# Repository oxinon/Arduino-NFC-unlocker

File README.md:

# Arduino-NFC-unlocker

<p><center></center></p>

Arduino NFC unlocker with NFC-bridge from Elecfreaks and a small circut for RGB LED and Optokopler, that works like a normal HID, no driver is needed. This will enter a previously stored password, an up arrow key can also be entered beforehand to unlock the screen.
<br>
YouTube Video of the NFC unlocker: https://www.youtube.com/watch?v=7boodr89aAs
<br>
<br>

* * *

<b>Index of this project</b>

+ [Read UID from NFC Tag](#readuid)
+ [Setting your password](#setpasswd)
+ [Eagle circut files](#eagle)
+ [Part list](#parts)

* * *
<br>
<h2>Read UID from NFC Tag</h2>

<p></a></p>

<h2>Setting your password</h2>

<h2>Eagle circut files</h2>

<p></a></p>

<h2>Part list</h2>
NFC brigde by elecfreaks
LED1: SMD RGB LED 1x<br>
LED2: SMD yelow LED 1208 1x<br>
R1,R2: SMD  10Ω Resistor 1208  2x<br>
R3,R4: SMD 220Ω Resistor 1208  2x<br>
OK1: Optokppler PC817 1x<br>
JP1: Pin Header 2,54 RM 5x<br>

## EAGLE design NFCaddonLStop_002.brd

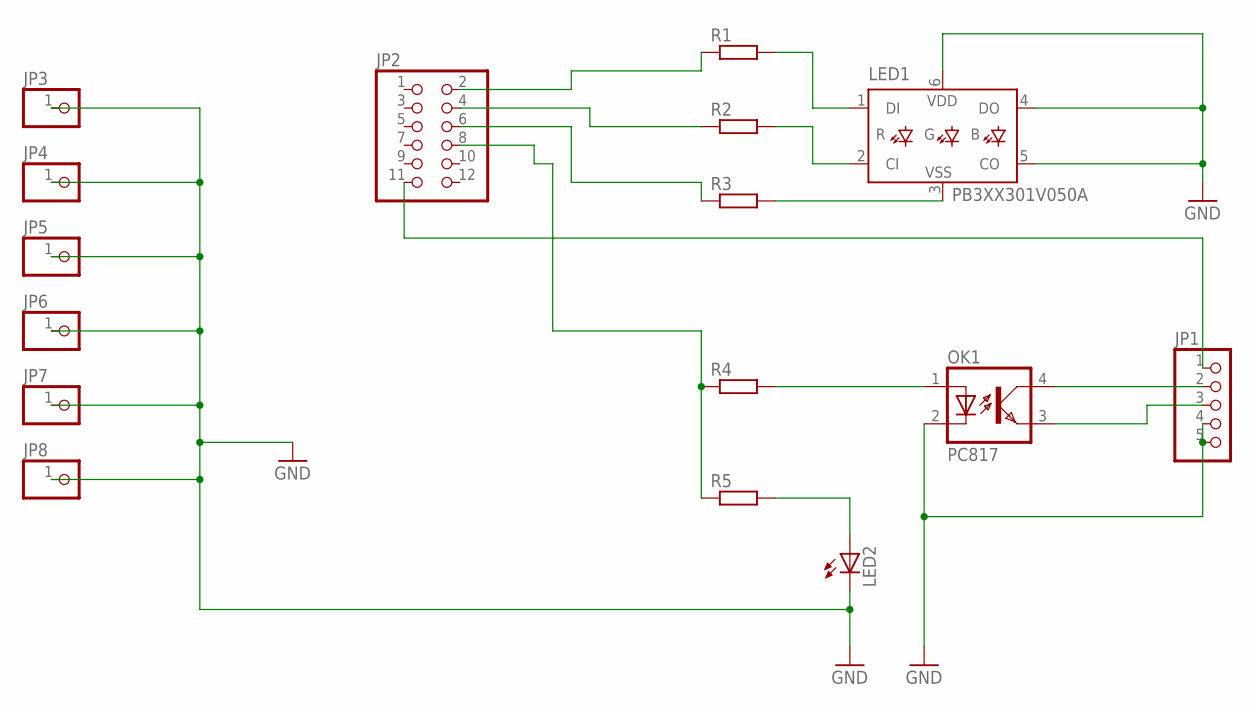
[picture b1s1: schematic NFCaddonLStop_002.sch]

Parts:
JP1: PINHD-1X5/90; 1X05/90
JP2: PINHD-2X6; 2X06
JP3, JP4, JP5, JP6, JP7, JP8: PINHD-1X1; 1X01
LED1: PB3XX301V050A
LED2: LEDCHIPLED_1206; CHIPLED_1206
OK1: PC817; DIL04
R1, R2, R3, R4, R5: R-EU_M1206; M1206

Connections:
GND: JP1.4, JP1.5, JP3.1, JP4.1, JP5.1, JP6.1, JP7.1, JP8.1, LED1.4 (DO), LED1.5 (CO), LED1.6 (VDD), LED2.C, OK1.2 (C)
unnamed: JP2.2, R1.1
unnamed: JP2.4, R2.1
unnamed: JP2.6, R3.1
unnamed: LED1.1 (DI), R1.2
unnamed: LED1.2 (CI), R2.2
unnamed: LED1.3 (VSS), R3.2
unnamed: JP2.8, R4.1, R5.1
unnamed: OK1.1 (A), R4.2
unnamed: LED2.A, R5.2
unnamed: JP1.2, OK1.4 (COL)
unnamed: JP1.3, OK1.3 (EMIT)
unnamed: JP1.1, JP2.11

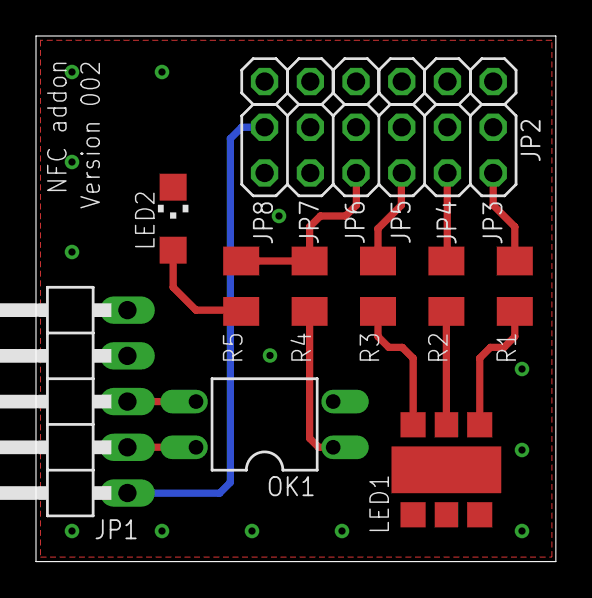
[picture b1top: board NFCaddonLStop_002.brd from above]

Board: 2 copper layers, 28.9 x 29.2 mm, 16 parts (0 on the bottom side), 13 nets.

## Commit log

2015-07-31 Arduino Sketch
2015-07-31 Eagle files
2019-02-12 Update README.md
    Update links
